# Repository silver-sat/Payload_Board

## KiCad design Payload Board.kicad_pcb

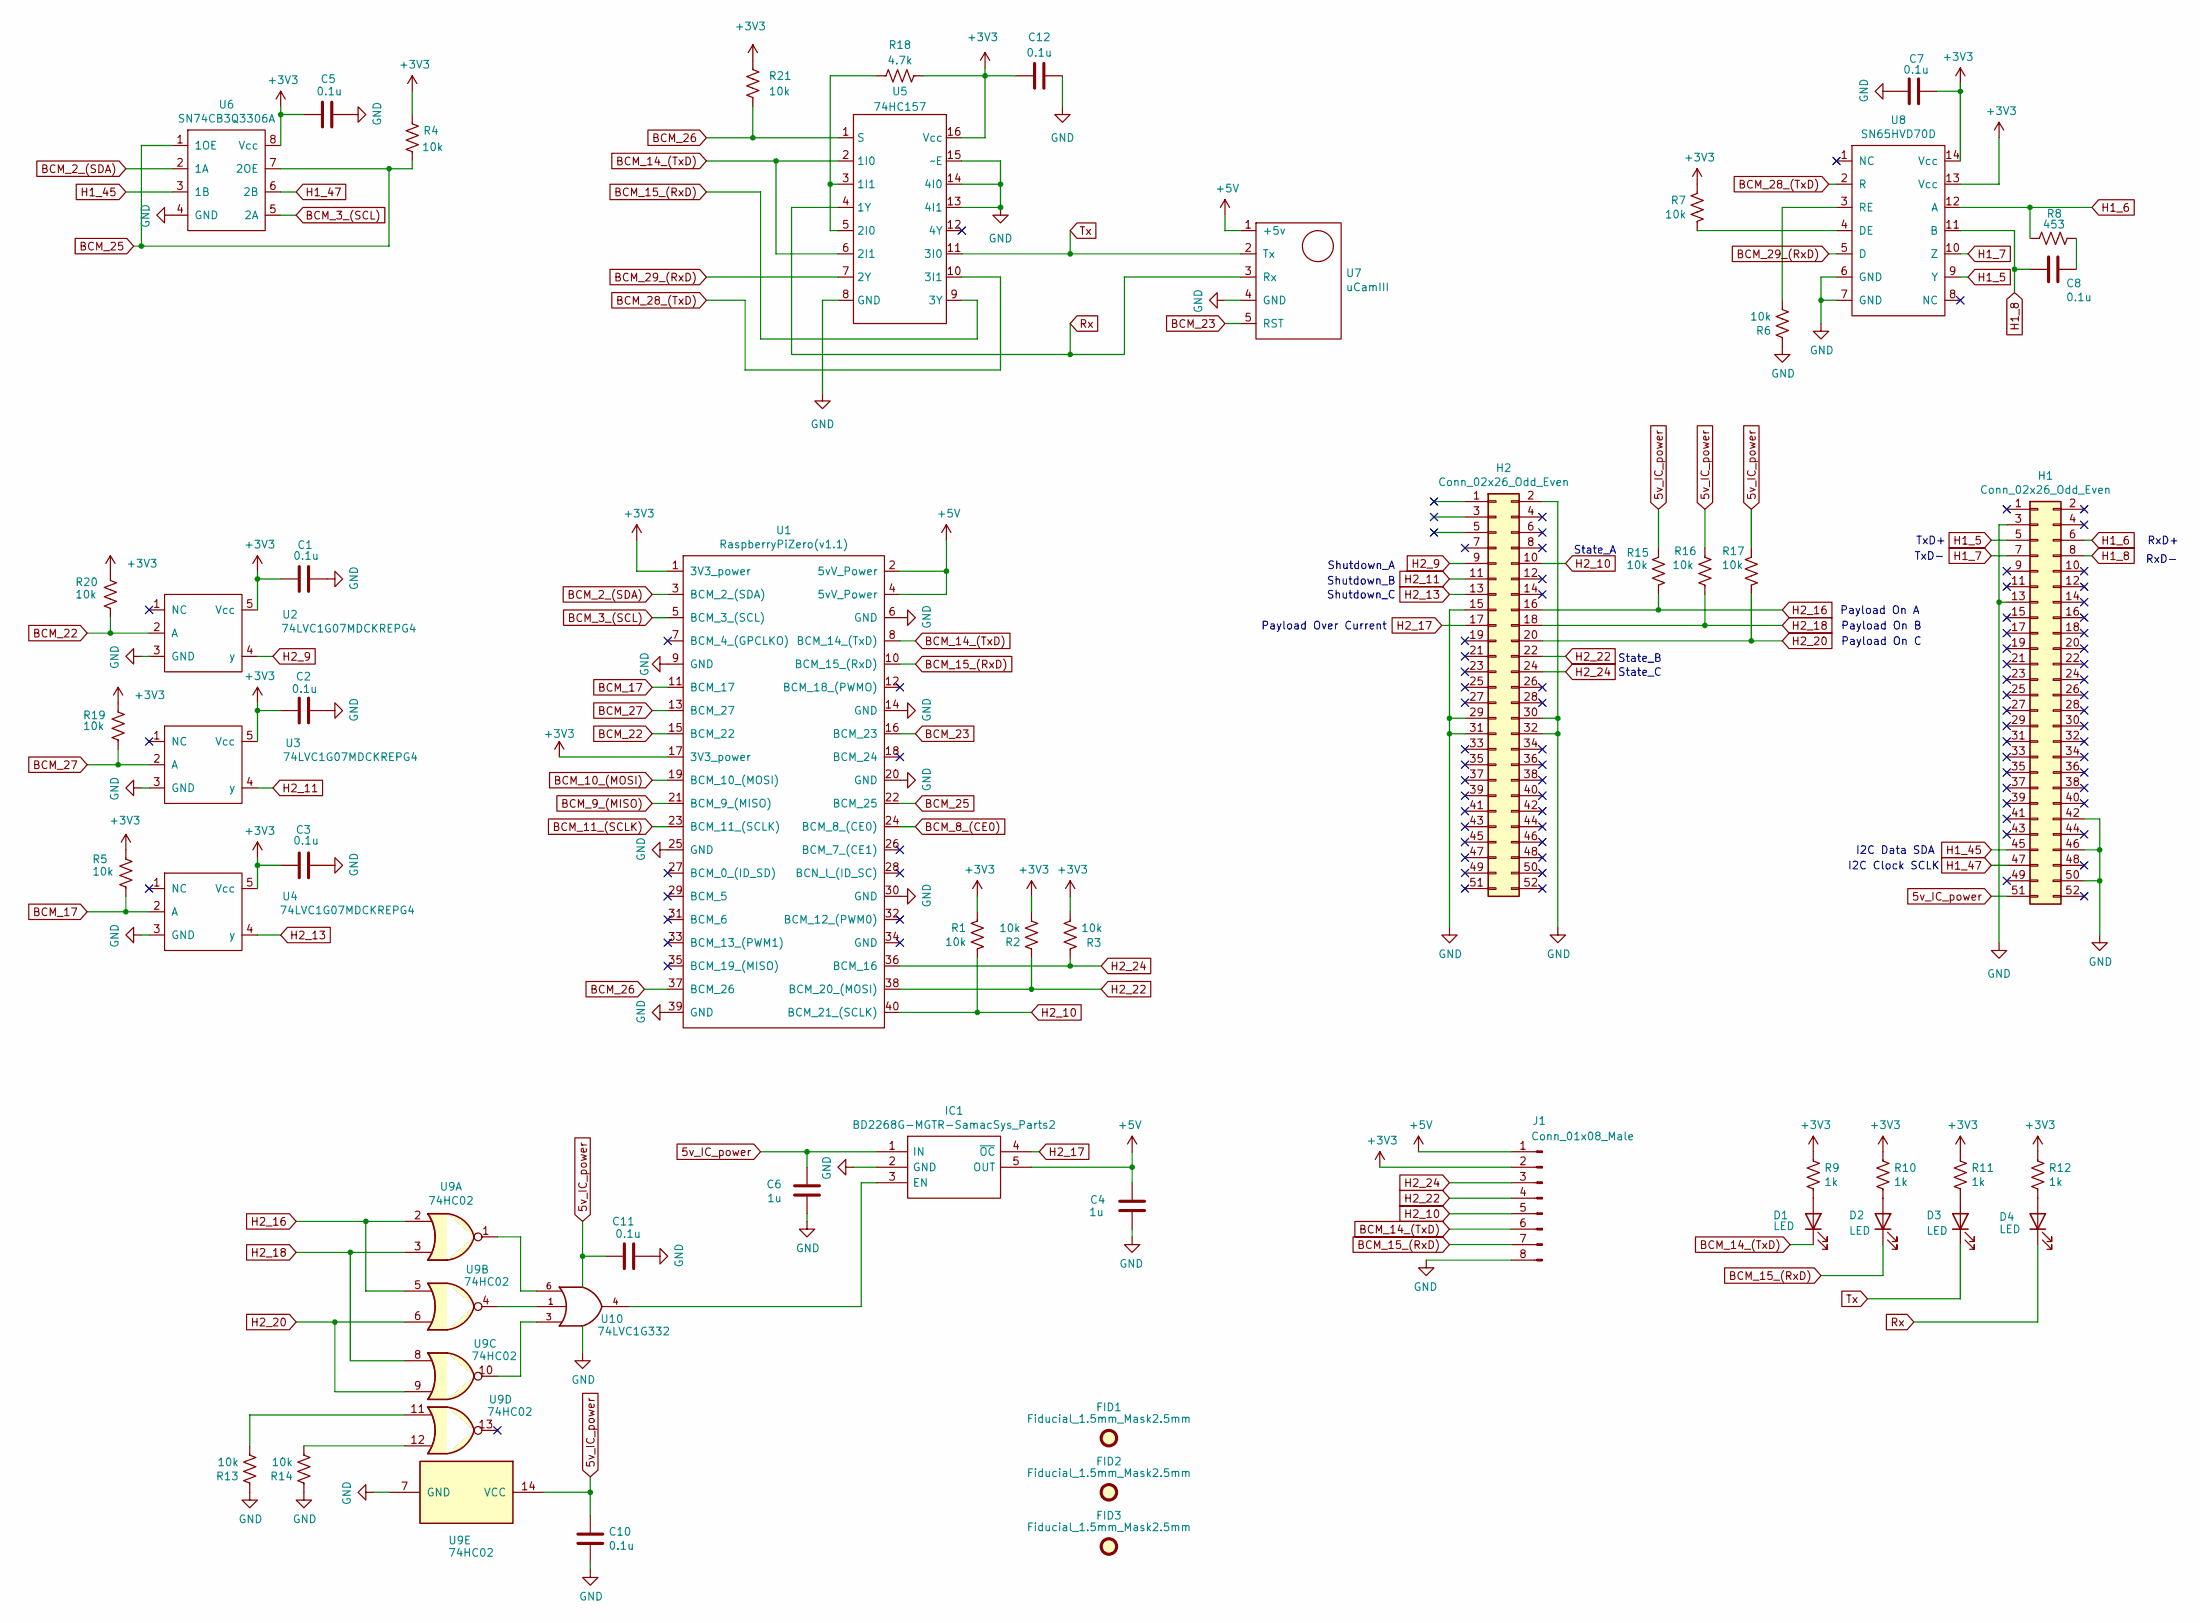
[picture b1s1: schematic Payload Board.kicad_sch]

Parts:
C1, C2, C3, C5, C7, C8, C10, C11, C12: 0.1u; C_0603_1608Metric; MPN 06031C104K4Z2A
C4, C6: 1u; C_0805_2012Metric; MPN 08053C105K4Z4A
D1, D2, D3, D4: LED; LED_D3.0mm
FID1, FID2, FID3: Fiducial_1.5mm_Mask2.5mm
H1, H2: Conn_02x26_Odd_Even; TheBus2x26
IC1: BD2268G-MGTR-SamacSys_Parts2; TSOP-5_1.65x3.05mm_P0.95mm; Manufacturer_Part_Number BD2268G-MGTR; Mouser Part Number 755-BD2268G-MGTR
J1: Conn_01x08_Male; PinHeader_1x08_P2.54mm_Vertical; MPN TSW-108-26-L-S
R1, R2, R3, R4, R5, R6, R7, R13, R14, R15, R16, R17, R19, R20, R21: 10k; R_0603_1608Metric; MPN ERJ-3RBD1002V
R8: 453; R_0603_1608Metric; MPN ERJ-3EKF4530V
R9, R10, R11, R12: 1k; R_0603_1608Metric; MPN ERJ-3EKF1001V
R18: 4.7k; R_0603_1608Metric; MPN ERJ-3EKF4701V
U1: RaspberryPiZero(v1.1); Raspberry_Pi_Zero_Socketed_THT_FaceDown_MountingHoles; MPN SLW-120-01-G-D
U2, U3, U4: 74LVC1G07MDCKREPG4; SOT-353_SC-70-5; MPN 74LVC1G07MDCKREP
U5: 74HC157; SOIC-16_3.9x9.9mm_P1.27mm; MPN MC75HC157ADR2G
U6: SN74CB3Q3306A; TSSOP-8_4.4x3mm_P0.65mm; MPN SN74CB3Q3306APWR
U7: uCamIII; UCAM-III; MPN BSW-105-04-G-S
U8: SN65HVD70D; SOIC-14_3.9x8.7mm_P1.27mm; MPN SN65HVD70D
U9: 74HC02; SOIC-14_3.9x8.7mm_P1.27mm; MPN SN74HC02QDRQ1
U10: 74LVC1G332; SOT-23-6; MPN SN74LVC1G332DBVR

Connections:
5v_IC_power: C6.1, C10.1, C11.1, H1.51, IC1.1 (IN), R15.2, R16.2, R17.1, U9.14 (VCC), U10.5 (VCC)
+3V3: C1.1, C2.1, C3.1, C5.1, C7.2, C12.2, J1.2, R1.1, R2.2, R3.2, R4.1, R5.1, R7.1, R9.1, R10.1, R11.1, R12.1, R18.1, R19.1, R20.1, R21.1, U1.1 (3V3_power), U1.17 (3V3_power), U2.5 (Vcc), U3.5 (Vcc), U4.5 (Vcc), U5.16 (Vcc), U6.8 (Vcc), U8.13 (Vcc), U8.14 (Vcc)
+5V: C4.1, IC1.5 (OUT), J1.1, U1.2 (5vV_Power), U1.4 (5vV_Power), U7.1 (+5v)
BCM_2_(SDA): U1.3 (BCM_2_(SDA)), U6.2 (1A)
BCM_3_(SCL): U1.5 (BCM_3_(SCL)), U6.5 (2A)
BCM_8_(CE0): U1.24 (BCM_8_(CE0))
BCM_9_(MISO): U1.21 (BCM_9_(MISO))
BCM_10_(MOSI): U1.19 (BCM_10_(MOSI))
BCM_11_(SCLK): U1.23 (BCM_11_(SCLK))
BCM_14_(TxD): D1.1 (K), J1.6, U1.8 (BCM_14_(TxD)), U5.2 (1I0), U5.6 (2I1)
BCM_15_(RxD): D2.1 (K), J1.7, U1.10 (BCM_15_(RxD)), U5.9 (3Y)
BCM_17: R5.2, U1.11 (BCM_17), U4.2 (A)
BCM_22: R20.2, U1.15 (BCM_22), U2.2 (A)
BCM_23: U1.16 (BCM_23), U7.5 (RST)
BCM_25: R4.2, U1.22 (BCM_25), U6.1 (1OE), U6.7 (2OE)
BCM_26: R21.2, U1.37 (BCM_26), U5.1 (S)
BCM_27: R19.2, U1.13 (BCM_27), U3.2 (A)
BCM_28_(TxD): U5.10 (3I1), U8.2 (R)
BCM_29_(RxD): U5.7 (2Y), U8.5 (D)
GND: C1.2, C2.2, C3.2, C4.2, C5.2, C6.2, C7.1, C10.2, C11.2, C12.1, H1.3, H1.13, H1.42, H1.46, H1.50, H2.2, H2.15, H2.29, H2.30, H2.31, H2.32, IC1.2 (GND), J1.8, R6.1, R13.1, R14.1, U1.6 (GND), U1.9 (GND), U1.14 (GND), U1.20 (GND), U1.25 (GND), U1.30 (GND), U1.39 (GND), U2.3 (GND), U3.3 (GND), U4.3 (GND), U5.8 (GND), U5.13 (4I1), U5.14 (4I0), U5.15 (~E), U6.4 (GND), U7.4 (GND), U8.6 (GND), U8.7 (GND), U9.7 (GND), U10.2 (GND)
H1_5: H1.5, U8.9 (Y)
H1_6: H1.6, R8.1, U8.12 (A)
H1_7: H1.7, U8.10 (Z)
H1_8: C8.2, H1.8, U8.11 (B)
H1_45: H1.45, U6.3 (1B)
H1_47: H1.47, U6.6 (2B)
H2_9: H2.9, U2.4 (y)
H2_10: H2.10, J1.5, R1.2, U1.40 (BCM_21_(SCLK))
H2_11: H2.11, U3.4 (y)
H2_13: H2.13, U4.4 (y)
H2_16: H2.16, R15.1, U9.2, U9.5
H2_17: H2.17, IC1.4 (~OC)
H2_18: H2.18, R16.1, U9.3, U9.8
H2_20: H2.20, R17.2, U9.6, U9.9
H2_22: H2.22, J1.4, R2.1, U1.38 (BCM_20_(MOSI))
H2_24: H2.24, J1.3, R3.1, U1.36 (BCM_16)
unnamed: C8.1, R8.2
unnamed: D1.2 (A), R9.2
unnamed: D2.2 (A), R10.2
unnamed: D3.2 (A), R11.2
unnamed: D4.2 (A), R12.2
unnamed: IC1.3 (EN), U10.4
unnamed: R13.2, U9.11
unnamed: R14.2, U9.12
unnamed: R18.2, U5.3 (1I1), U5.5 (2I0)
unnamed: R7.2, U8.4 (DE)
unnamed: R6.2, U8.3 (RE)
unnamed: U9.4, U10.1
unnamed: U9.10, U10.3
unnamed: U9.1, U10.6
Rx: D4.1 (K), U5.4 (1Y), U7.3 (Rx)
Tx: D3.1 (K), U5.11 (3I0), U7.2 (Tx)

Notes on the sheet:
Payload On A
Shutdown_A
I2C Data SDA
State_A
Shutdown_B
Payload On C
State_B
TxD+
TxD-
RxD-
State_C
I2C Clock SCLK
RxD+
Shutdown_C
Payload On B
Payload Over Current

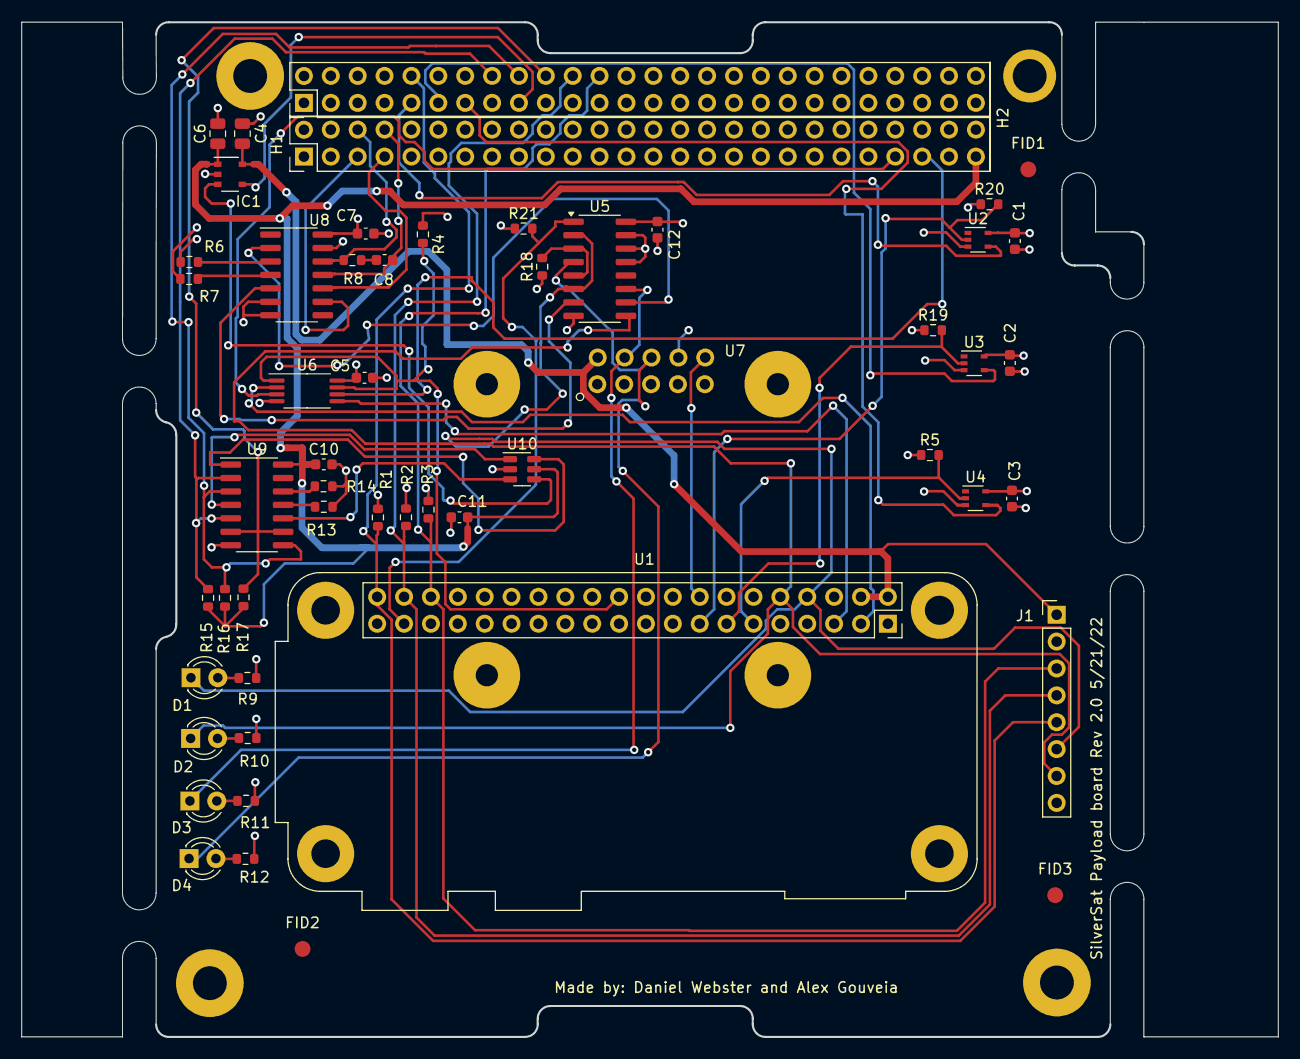
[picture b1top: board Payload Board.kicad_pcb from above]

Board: 4 copper layers, 118.7 x 95.9 mm, 57 parts (0 on the bottom side), 48 nets.

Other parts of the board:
M1, M2, M3, M4: MountingHole_3.2mm_M3_Pad

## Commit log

2022-05-22 Added .zip to .gitignore
2023-02-11 Add files via upload
    Payload board relocation
2023-02-18 Add files via upload
    Fixed Max3100 pins and H2 EPS Pins
2023-02-22 Updated .gitignore - added \#auto_saved_files\#
2023-02-23 File Management
    I made some file management changes to make it easier to understand.
2023-03-02 Pin changes for Max3100/Organization
    Pins 1 and 3 on the max3100(U5) called BCM_11_SCLK and BCM_10_MOSI were switched, which resolves it both in the schematic and the PCB editor. There were also minor organizational changes.
2024-04-20 added fiducials and started rails
2024-04-27 New Updates to schematic
2024-04-27 Finalized UCAM schematic
2024-04-27 Finalized Rails
2024-04-27 Added Pullup resistors on shutdown lines
2024-04-27 changes to pullup resistors
2024-04-29 Updated schematic
2024-05-11 firstCommit-Noah
2024-06-01 continued to wire UART switch into schematic
2024-06-08 Continued development and began fixing errors
2024-06-08 Glossing
2024-06-08 Fixed minor errors
2024-06-12 Updated BOM, added bypasses, cleaned up schematic
    Updated parts to include MPN and Manufacturer fields and made them match MPL
    Added bypasses on IC1
    Cleaned up schematic to make it more readable (so I could verify connections!)
2024-06-12 Added 3d bodies to RPi and camera
    Added the 3d bodies for the Rpi and camera connectors
2024-06-12 Minor improvements
2024-06-13 Update Payload Board.kicad_sch
    I didn't save it before, so it never got updated.
2024-06-13 Really updated this time
    Okay, I forgot to save the files earlier, but no harm....
    This has all the 3D models attached, the updated values for R9 through R12,
    and the updated schematic.
2024-06-13 moved some silk layer items
    I prefer silk to NOT be on top of vias, so I moved those objects
2024-06-13 added 3d models of plugin boards
    Added 3d models of the RPi and the camera.
2024-06-13 moved a designator
    it was on top of another, so I fixed it...
2024-06-13 new production files
    new gerbers, position and drill files
2024-06-14 updated drills
    updated drill files
2024-06-14 Delete Payload Board.drl
    remove old drill file
2024-06-16 Schematic cleanup and 3D model add-ins
    I cleaned up the schematic a little more to make it easier to read.
    I also tried fixing the path so that the extra 3D models show up.
    Be sure to update kicad_library as well. That contains the Silversat parts.
2024-06-22 Updated 3D files
    Updated the 3D files to include the daughter boards.
